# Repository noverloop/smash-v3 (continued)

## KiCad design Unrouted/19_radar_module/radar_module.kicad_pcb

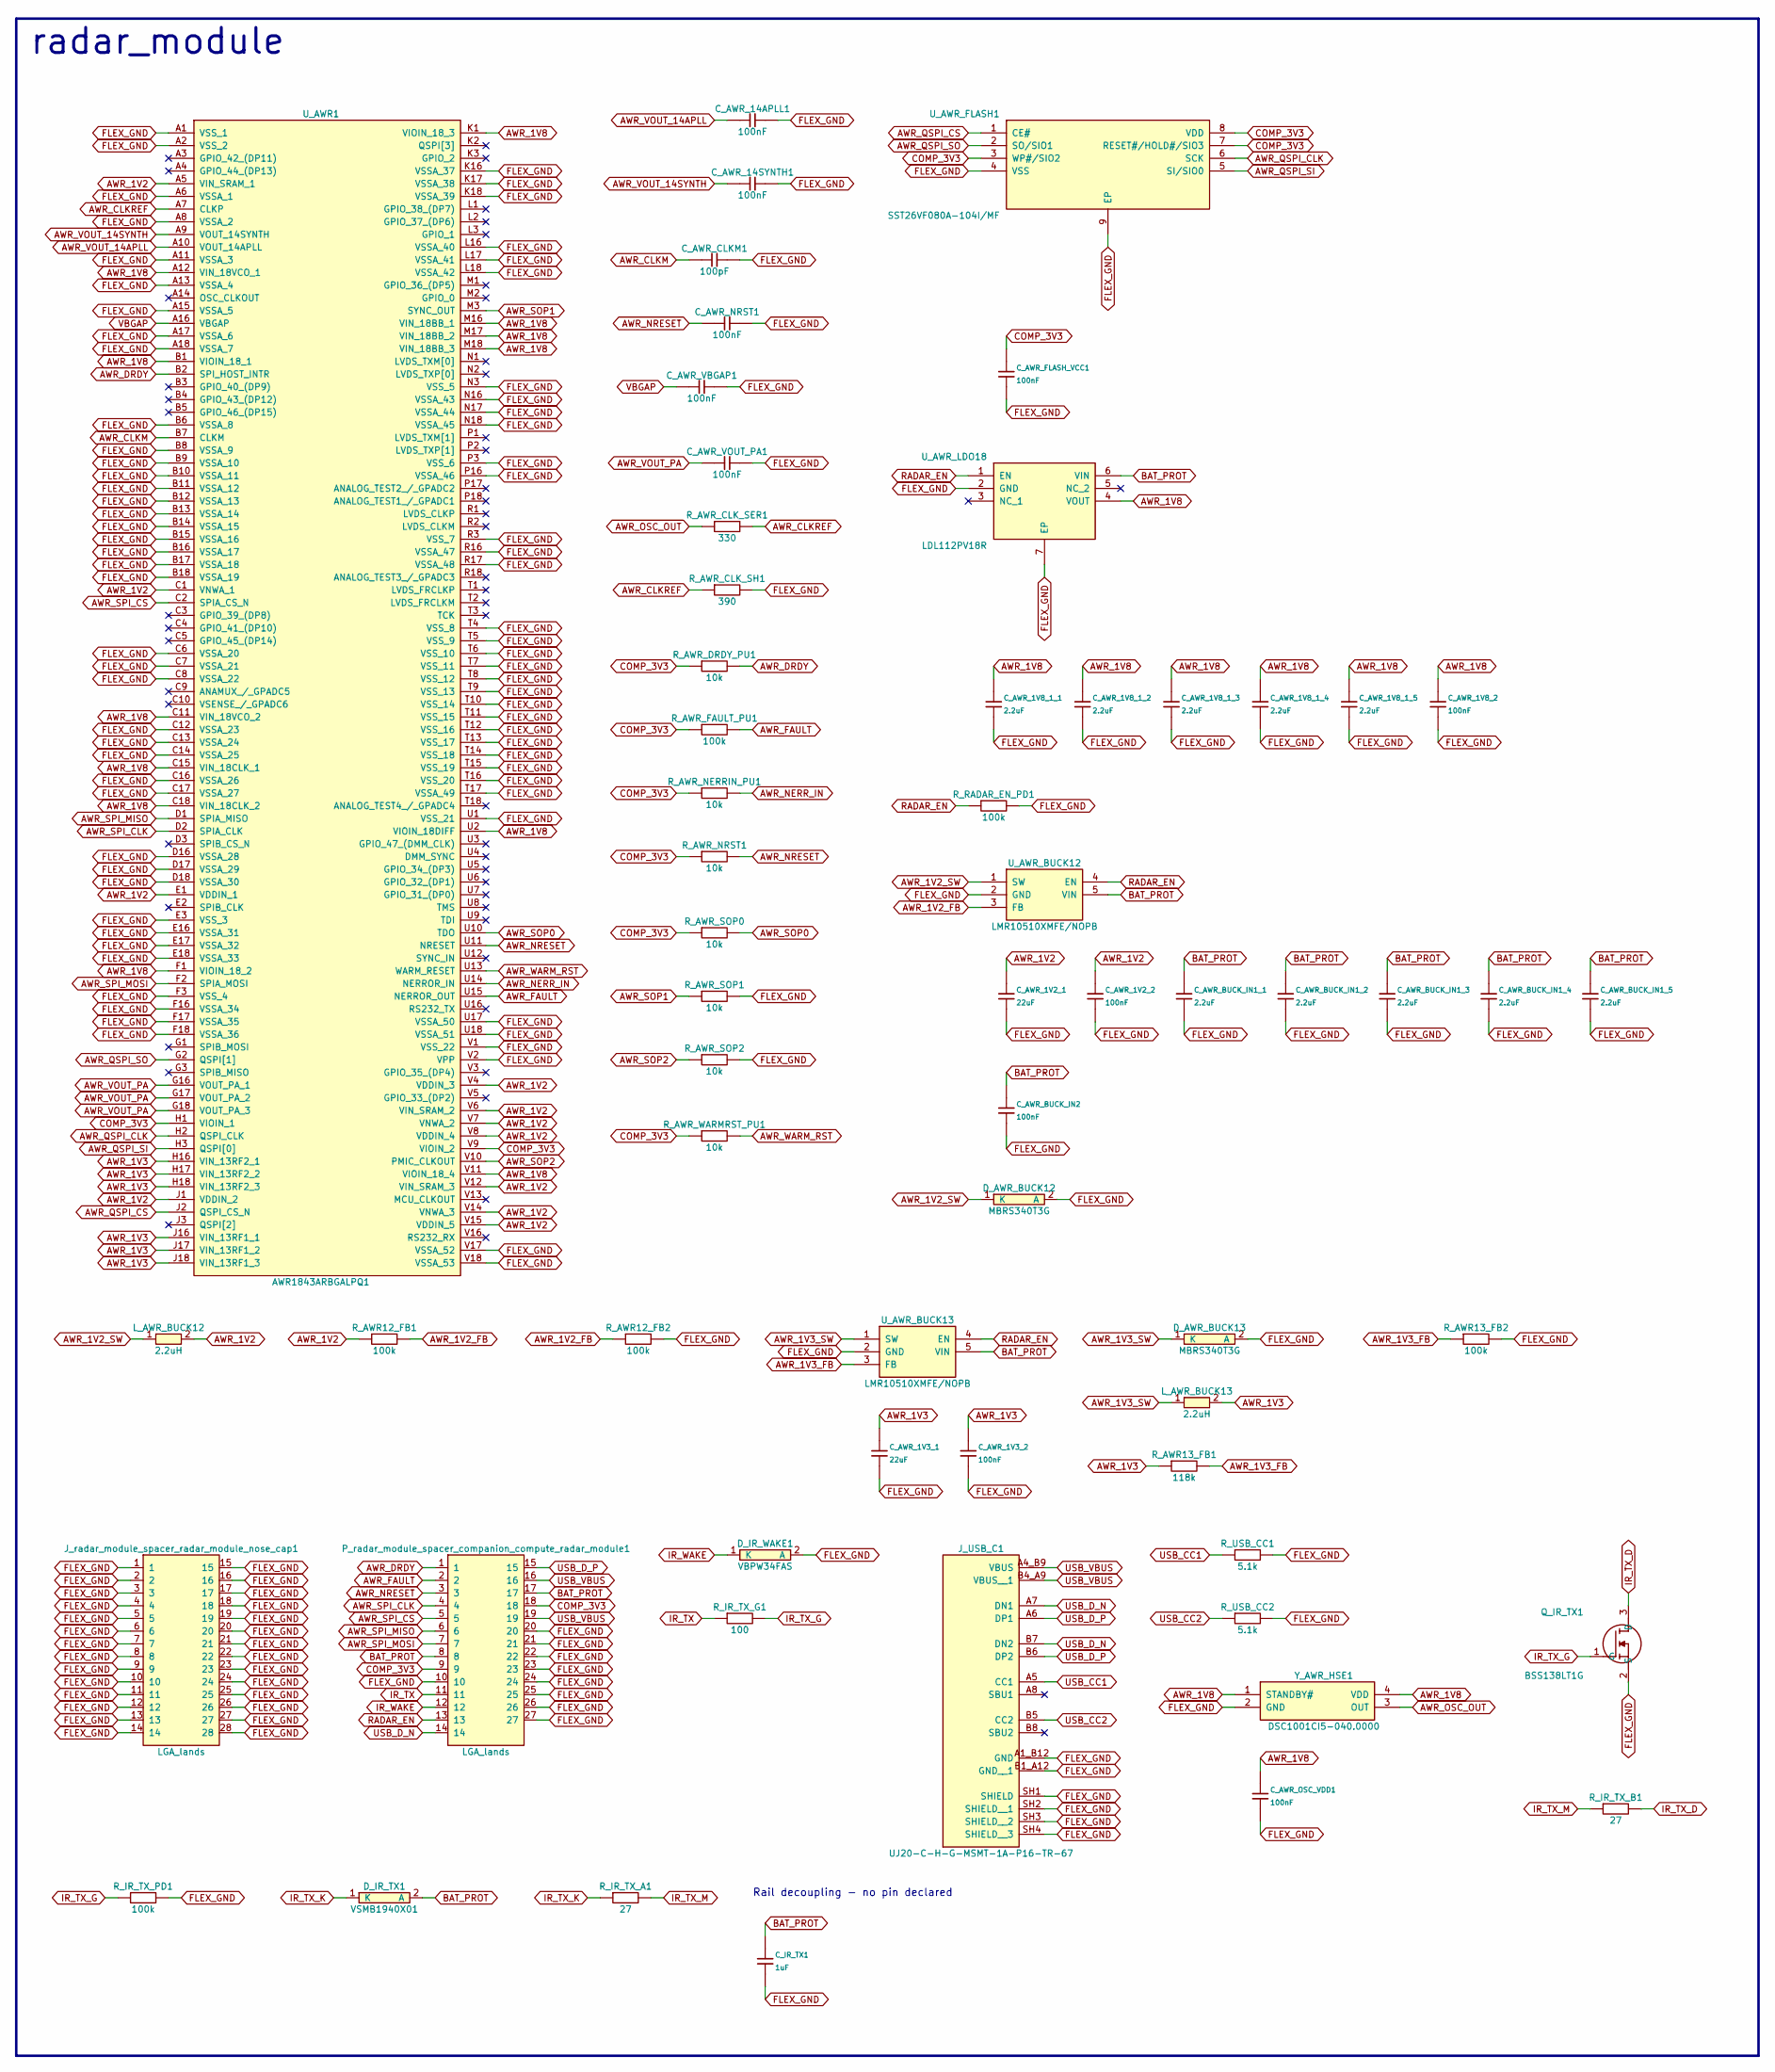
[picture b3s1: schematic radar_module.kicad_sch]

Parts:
C_AWR_1V2_1, C_AWR_1V3_1: 22uF; Capacitor_Tantalum_SMD_CP_EIA-3528-12_Kemet-T; MPN T491T 22uF (3528-12 thinnest variant)
C_AWR_1V2_2, C_AWR_1V3_2, C_AWR_1V8_2, C_AWR_14APLL1, C_AWR_14SYNTH1: 100nF; Capacitor_SMD_C_0402_1005Metric; MPN C0402 X7R 100nF
C_AWR_1V8_1_1, C_AWR_1V8_1_2, C_AWR_1V8_1_3, C_AWR_1V8_1_4, C_AWR_1V8_1_5: 2.2uF; Capacitor_SMD_C_0603_1608Metric; MPN C-Series MIL-PRF-32535 X7R 0603 2.2uF
C_AWR_BUCK_IN1_1, C_AWR_BUCK_IN1_2, C_AWR_BUCK_IN1_3, C_AWR_BUCK_IN1_4, C_AWR_BUCK_IN1_5: 2.2uF; Capacitor_SMD_C_0603_1608Metric; MPN C-Series MIL-PRF-32535 X7R 0603 2.2uF
C_AWR_BUCK_IN2: 100nF; Capacitor_SMD_C_0402_1005Metric; MPN C0402 X7R 100nF
C_AWR_CLKM1: 100pF; Capacitor_SMD_C_0603_1608Metric; MPN SQCSVA 100pF
C_AWR_FLASH_VCC1: 100nF; Capacitor_SMD_C_0402_1005Metric; MPN C0402 X7R 100nF
C_AWR_NRST1: 100nF; Capacitor_SMD_C_0402_1005Metric; MPN C0402 X7R 100nF
C_AWR_OSC_VDD1: 100nF; Capacitor_SMD_C_0402_1005Metric; MPN C0402 X7R 100nF
C_AWR_VBGAP1: 100nF; Capacitor_SMD_C_0402_1005Metric; MPN C0402 X7R 100nF
C_AWR_VOUT_PA1: 100nF; Capacitor_SMD_C_0402_1005Metric; MPN C0402 X7R 100nF
C_IR_TX1: 1uF; Capacitor_SMD_C_0805_2012Metric; MPN C-Series MIL-PRF-32535 X7R 0805 1uF
D_AWR_BUCK12, D_AWR_BUCK13: MBRS340T3G; DIOM8059X261N; MPN MBRS340T3G
D_IR_TX1: VSMB1940X01; MPN VSMB1940X01
D_IR_WAKE1: VBPW34FAS; MPN VBPW34FAS
J_USB_C1: UJ20-C-H-G-MSMT-1A-P16-TR-67; SAMESKY_UJ20-C-H-G-MSMT-1A-P16-TR-67; MPN UJ20-C-H-G-MSMT-1A-P16-TR-67
J_radar_module_spacer_radar_module_nose_cap1: LGA_lands; J_radar_module_spacer_radar_module_nose_cap; MPN LGA_lands
L_AWR_BUCK12, L_AWR_BUCK13: 2.2uH; Inductor_SMD_L_2012_2.0x1.25mm; MPN TMS201210ALM-2R2MTAA
P_radar_module_spacer_companion_compute_radar_module1: LGA_lands; P_radar_module_spacer_companion_compute_radar_module; MPN LGA_lands
Q_IR_TX1: BSS138LT1G; SOT96P237X111-3N; MPN BSS138LT1G
R_AWR12_FB1, R_AWR12_FB2, R_AWR13_FB2: 100k; Resistor_SMD_R_0402_1005Metric; MPN CRCW0402 100k 1% e3
R_AWR13_FB1: 118k; Resistor_SMD_R_0402_1005Metric; MPN CRCW0402 118k 1% e3
R_AWR_CLK_SER1: 330; Resistor_SMD_R_0402_1005Metric; MPN CRCW0402 330 1% e3
R_AWR_CLK_SH1: 390; Resistor_SMD_R_0402_1005Metric; MPN CRCW0402 390 1% e3
R_AWR_DRDY_PU1: 10k; Resistor_SMD_R_0402_1005Metric; MPN CRCW0402 10k 1% e3
R_AWR_FAULT_PU1: 100k; Resistor_SMD_R_0402_1005Metric; MPN CRCW0402 100k 1% e3
R_AWR_NERRIN_PU1: 10k; Resistor_SMD_R_0402_1005Metric; MPN CRCW0402 10k 1% e3
R_AWR_NRST1: 10k; Resistor_SMD_R_0402_1005Metric; MPN CRCW0402 10k 1% e3
R_AWR_SOP0, R_AWR_SOP1, R_AWR_SOP2: 10k; Resistor_SMD_R_0402_1005Metric; MPN CRCW0402 10k 1% e3
R_AWR_WARMRST_PU1: 10k; Resistor_SMD_R_0402_1005Metric; MPN CRCW0402 10k 1% e3
R_IR_TX_A1: 27; Resistor_SMD_R_0402_1005Metric; MPN CRCW0402 27 1% e3
R_IR_TX_B1: 27; Resistor_SMD_R_0402_1005Metric; MPN CRCW0402 27 1% e3
R_IR_TX_G1: 100; Resistor_SMD_R_0402_1005Metric; MPN CRCW0402 100 1% e3
R_IR_TX_PD1: 100k; Resistor_SMD_R_0402_1005Metric; MPN CRCW0402 100k 1% e3
R_RADAR_EN_PD1: 100k; Resistor_SMD_R_0402_1005Metric; MPN CRCW0402 100k 1% e3
R_USB_CC1, R_USB_CC2: 5.1k; Resistor_SMD_R_0402_1005Metric; MPN CRCW0402 5.1k 1% e3
U_AWR1: AWR1843ARBGALPQ1; BGA180C80P18X18_1500X1500X96; MPN AWR1843ARBGALPQ1
U_AWR_BUCK12, U_AWR_BUCK13: LMR10510XMFE/NOPB; SOT95P280X145-5N; MPN LMR10510XMFE/NOPB
U_AWR_FLASH1: SST26VF080A-104I/MF; SON127P600X500X80-9N-D; MPN SST26VF080A-104I/MF
U_AWR_LDO18: LDL112PV18R; SON95P300X300X100-7N-D; MPN LDL112PV18R
Y_AWR_HSE1: DSC1001CI5-040.0000; DSC1001CI50080000; MPN DSC1001CI5-040.0000

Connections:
AWR_1V2: C_AWR_1V2_1.1, C_AWR_1V2_2.1, L_AWR_BUCK12.2, R_AWR12_FB1.1, U_AWR1.A5 (VIN_SRAM_1), U_AWR1.C1 (VNWA_1), U_AWR1.E1 (VDDIN_1), U_AWR1.J1 (VDDIN_2), U_AWR1.V4 (VDDIN_3), U_AWR1.V6 (VIN_SRAM_2), U_AWR1.V7 (VNWA_2), U_AWR1.V8 (VDDIN_4), U_AWR1.V12 (VIN_SRAM_3), U_AWR1.V14 (VNWA_3), U_AWR1.V15 (VDDIN_5)
AWR_1V2_FB: R_AWR12_FB1.2, R_AWR12_FB2.1, U_AWR_BUCK12.3 (FB)
AWR_1V2_SW: D_AWR_BUCK12.1 (K), L_AWR_BUCK12.1, U_AWR_BUCK12.1 (SW)
AWR_1V3: C_AWR_1V3_1.1, C_AWR_1V3_2.1, L_AWR_BUCK13.2, R_AWR13_FB1.1, U_AWR1.H16 (VIN_13RF2_1), U_AWR1.H17 (VIN_13RF2_2), U_AWR1.H18 (VIN_13RF2_3), U_AWR1.J16 (VIN_13RF1_1), U_AWR1.J17 (VIN_13RF1_2), U_AWR1.J18 (VIN_13RF1_3)
AWR_1V3_FB: R_AWR13_FB1.2, R_AWR13_FB2.1, U_AWR_BUCK13.3 (FB)
AWR_1V3_SW: D_AWR_BUCK13.1 (K), L_AWR_BUCK13.1, U_AWR_BUCK13.1 (SW)
AWR_1V8: C_AWR_1V8_1_1.1, C_AWR_1V8_1_2.1, C_AWR_1V8_1_3.1, C_AWR_1V8_1_4.1, C_AWR_1V8_1_5.1, C_AWR_1V8_2.1, C_AWR_OSC_VDD1.1, U_AWR1.A12 (VIN_18VCO_1), U_AWR1.B1 (VIOIN_18_1), U_AWR1.C11 (VIN_18VCO_2), U_AWR1.C15 (VIN_18CLK_1), U_AWR1.C18 (VIN_18CLK_2), U_AWR1.F1 (VIOIN_18_2), U_AWR1.K1 (VIOIN_18_3), U_AWR1.M16 (VIN_18BB_1), U_AWR1.M17 (VIN_18BB_2), U_AWR1.M18 (VIN_18BB_3), U_AWR1.U2 (VIOIN_18DIFF), U_AWR1.V11 (VIOIN_18_4), U_AWR_LDO18.4 (VOUT), Y_AWR_HSE1.1 (STANDBY#), Y_AWR_HSE1.4 (VDD)
AWR_CLKM: C_AWR_CLKM1.1, U_AWR1.B7 (CLKM)
AWR_CLKREF: R_AWR_CLK_SER1.2, R_AWR_CLK_SH1.1, U_AWR1.A7 (CLKP)
AWR_DRDY: P_radar_module_spacer_companion_compute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.1, R_AWR_DRDY_PU1.2, U_AWR1.B2 (SPI_HOST_INTR)
AWR_FAULT: P_radar_module_spacer_companion_compute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.2, R_AWR_FAULT_PU1.2, U_AWR1.U15 (NERROR_OUT)
AWR_NERR_IN: R_AWR_NERRIN_PU1.2, U_AWR1.U14 (NERROR_IN)
AWR_NRESET: C_AWR_NRST1.1, P_radar_module_spacer_companion_compute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.3, R_AWR_NRST1.2, U_AWR1.U11 (NRESET)
AWR_OSC_OUT: R_AWR_CLK_SER1.1, Y_AWR_HSE1.3 (OUT)
AWR_QSPI_CLK: U_AWR1.H2 (QSPI_CLK), U_AWR_FLASH1.6 (SCK)
AWR_QSPI_CS: U_AWR1.J2 (QSPI_CS_N), U_AWR_FLASH1.1 (CE#)
AWR_QSPI_SI: U_AWR1.H3 (QSPI[0]), U_AWR_FLASH1.5 (SI/SIO0)
AWR_QSPI_SO: U_AWR1.G2 (QSPI[1]), U_AWR_FLASH1.2 (SO/SIO1)
AWR_SOP0: R_AWR_SOP0.2, U_AWR1.U10 (TDO)
AWR_SOP1: R_AWR_SOP1.1, U_AWR1.M3 (SYNC_OUT)
AWR_SOP2: R_AWR_SOP2.1, U_AWR1.V10 (PMIC_CLKOUT)
AWR_SPI_CLK: P_radar_module_spacer_companion_compute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.4, U_AWR1.D2 (SPIA_CLK)
AWR_SPI_CS: P_radar_module_spacer_companion_compute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.5, U_AWR1.C2 (SPIA_CS_N)
AWR_SPI_MISO: P_radar_module_spacer_companion_compute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.6, U_AWR1.D1 (SPIA_MISO)
AWR_SPI_MOSI: P_radar_module_spacer_companion_compute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.7, U_AWR1.F2 (SPIA_MOSI)
AWR_VOUT_14APLL: C_AWR_14APLL1.1, U_AWR1.A10 (VOUT_14APLL)
AWR_VOUT_14SYNTH: C_AWR_14SYNTH1.1, U_AWR1.A9 (VOUT_14SYNTH)
AWR_VOUT_PA: C_AWR_VOUT_PA1.1, U_AWR1.G16 (VOUT_PA_1), U_AWR1.G17 (VOUT_PA_2), U_AWR1.G18 (VOUT_PA_3)
AWR_WARM_RST: R_AWR_WARMRST_PU1.2, U_AWR1.U13 (WARM_RESET)
BAT_PROT: C_AWR_BUCK_IN1_1.1, C_AWR_BUCK_IN1_2.1, C_AWR_BUCK_IN1_3.1, C_AWR_BUCK_IN1_4.1, C_AWR_BUCK_IN1_5.1, C_AWR_BUCK_IN2.1, C_IR_TX1.1, D_IR_TX1.2 (A), P_radar_module_spacer_companion_compute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.8, P_radar_module_spacer_companion_compute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.17, U_AWR_BUCK12.5 (VIN), U_AWR_BUCK13.5 (VIN), U_AWR_LDO18.6 (VIN)
COMP_3V3: C_AWR_FLASH_VCC1.1, P_radar_module_spacer_companion_compute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.9, P_radar_module_spacer_companion_compute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.18, R_AWR_DRDY_PU1.1, R_AWR_FAULT_PU1.1, R_AWR_NERRIN_PU1.1, R_AWR_NRST1.1, R_AWR_SOP0.1, R_AWR_WARMRST_PU1.1, U_AWR1.H1 (VIOIN_1), U_AWR1.V9 (VIOIN_2), U_AWR_FLASH1.3 (WP#/SIO2), U_AWR_FLASH1.7 (RESET#/HOLD#/SIO3), U_AWR_FLASH1.8 (VDD)
FLEX_GND: C_AWR_1V2_1.2, C_AWR_1V2_2.2, C_AWR_1V3_1.2, C_AWR_1V3_2.2, C_AWR_1V8_1_1.2, C_AWR_1V8_1_2.2, C_AWR_1V8_1_3.2, C_AWR_1V8_1_4.2, C_AWR_1V8_1_5.2, C_AWR_1V8_2.2, C_AWR_14APLL1.2, C_AWR_14SYNTH1.2, C_AWR_BUCK_IN1_1.2, C_AWR_BUCK_IN1_2.2, C_AWR_BUCK_IN1_3.2, C_AWR_BUCK_IN1_4.2, C_AWR_BUCK_IN1_5.2, C_AWR_BUCK_IN2.2, C_AWR_CLKM1.2, C_AWR_FLASH_VCC1.2, C_AWR_NRST1.2, C_AWR_OSC_VDD1.2, C_AWR_VBGAP1.2, C_AWR_VOUT_PA1.2, C_IR_TX1.2, D_AWR_BUCK12.2 (A), D_AWR_BUCK13.2 (A), D_IR_WAKE1.2 (A), J_USB_C1.A1_B12 (GND), J_USB_C1.B1_A12 (GND__1), J_USB_C1.SH1 (SHIELD), J_USB_C1.SH2 (SHIELD__1), J_USB_C1.SH3 (SHIELD__2), J_USB_C1.SH4 (SHIELD__3), J_radar_module_spacer_radar_module_nose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.1, J_radar_module_spacer_radar_module_nose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.2, J_radar_module_spacer_radar_module_nose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.3, J_radar_module_spacer_radar_module_nose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.4, J_radar_module_spacer_radar_module_nose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.5, J_radar_module_spacer_radar_module_nose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.6, J_radar_module_spacer_radar_module_nose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.7, J_radar_module_spacer_radar_module_nose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.8, J_radar_module_spacer_radar_module_nose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.9, J_radar_module_spacer_radar_module_nose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.10, J_radar_module_spacer_radar_module_nose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.11, J_radar_module_spacer_radar_module_nose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.12, J_radar_module_spacer_radar_module_nose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.13, J_radar_module_spacer_radar_module_nose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.14, J_radar_module_spacer_radar_module_nose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.15, J_radar_module_spacer_radar_module_nose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.16, J_radar_module_spacer_radar_module_nose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.17, J_radar_module_spacer_radar_module_nose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.18, J_radar_module_spacer_radar_module_nose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.19, J_radar_module_spacer_radar_module_nose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.20, J_radar_module_spacer_radar_module_nose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.21, J_radar_module_spacer_radar_module_nose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.22, J_radar_module_spacer_radar_module_nose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.23, J_radar_module_spacer_radar_module_nose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.24, J_radar_module_spacer_radar_module_nose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.25, J_radar_module_spacer_radar_module_nose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.26, J_radar_module_spacer_radar_module_nose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.27, J_radar_module_spacer_radar_module_nose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.28, P_radar_module_spacer_companion_compute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.10, P_radar_module_spacer_companion_compute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.20, P_radar_module_spacer_companion_compute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.21, P_radar_module_spacer_companion_compute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.22, P_radar_module_spacer_companion_compute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.23, P_radar_module_spacer_companion_compute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.24, P_radar_module_spacer_companion_compute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.25, P_radar_module_spacer_companion_compute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.26, P_radar_module_spacer_companion_compute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.27, Q_IR_TX1.2 (S), R_AWR12_FB2.2, R_AWR13_FB2.2, R_AWR_CLK_SH1.2, R_AWR_SOP1.2, R_AWR_SOP2.2, R_IR_TX_PD1.2, R_RADAR_EN_PD1.2, R_USB_CC1.2, R_USB_CC2.2, U_AWR1.A1 (VSS_1), U_AWR1.A2 (VSS_2), U_AWR1.A6 (VSSA_1), U_AWR1.A8 (VSSA_2), U_AWR1.A11 (VSSA_3), U_AWR1.A13 (VSSA_4), U_AWR1.A15 (VSSA_5), U_AWR1.A17 (VSSA_6), U_AWR1.A18 (VSSA_7), U_AWR1.B6 (VSSA_8), U_AWR1.B8 (VSSA_9), U_AWR1.B9 (VSSA_10), U_AWR1.B10 (VSSA_11), U_AWR1.B11 (VSSA_12), U_AWR1.B12 (VSSA_13), U_AWR1.B13 (VSSA_14), U_AWR1.B14 (VSSA_15), U_AWR1.B15 (VSSA_16), U_AWR1.B16 (VSSA_17), U_AWR1.B17 (VSSA_18), U_AWR1.B18 (VSSA_19), U_AWR1.C6 (VSSA_20), U_AWR1.C7 (VSSA_21), U_AWR1.C8 (VSSA_22), U_AWR1.C12 (VSSA_23), U_AWR1.C13 (VSSA_24), U_AWR1.C14 (VSSA_25), U_AWR1.C16 (VSSA_26), U_AWR1.C17 (VSSA_27), U_AWR1.D16 (VSSA_28), U_AWR1.D17 (VSSA_29), U_AWR1.D18 (VSSA_30), U_AWR1.E3 (VSS_3), U_AWR1.E16 (VSSA_31), U_AWR1.E17 (VSSA_32), U_AWR1.E18 (VSSA_33), U_AWR1.F3 (VSS_4), U_AWR1.F16 (VSSA_34), U_AWR1.F17 (VSSA_35), U_AWR1.F18 (VSSA_36), U_AWR1.K16 (VSSA_37), U_AWR1.K17 (VSSA_38), U_AWR1.K18 (VSSA_39), U_AWR1.L16 (VSSA_40), U_AWR1.L17 (VSSA_41), U_AWR1.L18 (VSSA_42), U_AWR1.N3 (VSS_5), U_AWR1.N16 (VSSA_43), U_AWR1.N17 (VSSA_44), U_AWR1.N18 (VSSA_45), U_AWR1.P3 (VSS_6), U_AWR1.P16 (VSSA_46), U_AWR1.R3 (VSS_7), U_AWR1.R16 (VSSA_47), U_AWR1.R17 (VSSA_48), U_AWR1.T4 (VSS_8), U_AWR1.T5 (VSS_9), U_AWR1.T6 (VSS_10), U_AWR1.T7 (VSS_11), U_AWR1.T8 (VSS_12), U_AWR1.T9 (VSS_13), U_AWR1.T10 (VSS_14), U_AWR1.T11 (VSS_15), U_AWR1.T12 (VSS_16), U_AWR1.T13 (VSS_17), U_AWR1.T14 (VSS_18), U_AWR1.T15 (VSS_19), U_AWR1.T16 (VSS_20), U_AWR1.T17 (VSSA_49), U_AWR1.U1 (VSS_21), U_AWR1.U17 (VSSA_50), U_AWR1.U18 (VSSA_51), U_AWR1.V1 (VSS_22), U_AWR1.V2 (VPP), U_AWR1.V17 (VSSA_52), U_AWR1.V18 (VSSA_53), U_AWR_BUCK12.2 (GND), U_AWR_BUCK13.2 (GND), U_AWR_FLASH1.4 (VSS), U_AWR_FLASH1.9 (EP), U_AWR_LDO18.2 (GND), U_AWR_LDO18.7 (EP), Y_AWR_HSE1.2 (GND)
IR_TX: P_radar_module_spacer_companion_compute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.11, R_IR_TX_G1.1
IR_TX_D: Q_IR_TX1.3 (D), R_IR_TX_B1.2
IR_TX_G: Q_IR_TX1.1 (G), R_IR_TX_G1.2, R_IR_TX_PD1.1
IR_TX_K: D_IR_TX1.1 (K), R_IR_TX_A1.1
IR_TX_M: R_IR_TX_A1.2, R_IR_TX_B1.1
IR_WAKE: D_IR_WAKE1.1 (K), P_radar_module_spacer_companion_compute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.12
RADAR_EN: P_radar_module_spacer_companion_compute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.13, R_RADAR_EN_PD1.1, U_AWR_BUCK12.4 (EN), U_AWR_BUCK13.4 (EN), U_AWR_LDO18.1 (EN)
USB_CC1: J_USB_C1.A5 (CC1), R_USB_CC1.1
USB_CC2: J_USB_C1.B5 (CC2), R_USB_CC2.1
USB_D_N: J_USB_C1.A7 (DN1), J_USB_C1.B7 (DN2), P_radar_module_spacer_companion_compute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.14
USB_D_P: J_USB_C1.A6 (DP1), J_USB_C1.B6 (DP2), P_radar_module_spacer_companion_compute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.15
USB_VBUS: J_USB_C1.A4_B9 (VBUS), J_USB_C1.B4_A9 (VBUS__1), P_radar_module_spacer_companion_compute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.16, P_radar_module_spacer_companion_compute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.19
VBGAP: C_AWR_VBGAP1.1, U_AWR1.A16 (VBGAP)

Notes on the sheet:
radar_module
Rail decoupling - no pin declared

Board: 20 copper layers, 64 parts (54 on the bottom side), 45 nets, no tracks yet.

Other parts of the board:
MH1, MH2: smash_mech_potting

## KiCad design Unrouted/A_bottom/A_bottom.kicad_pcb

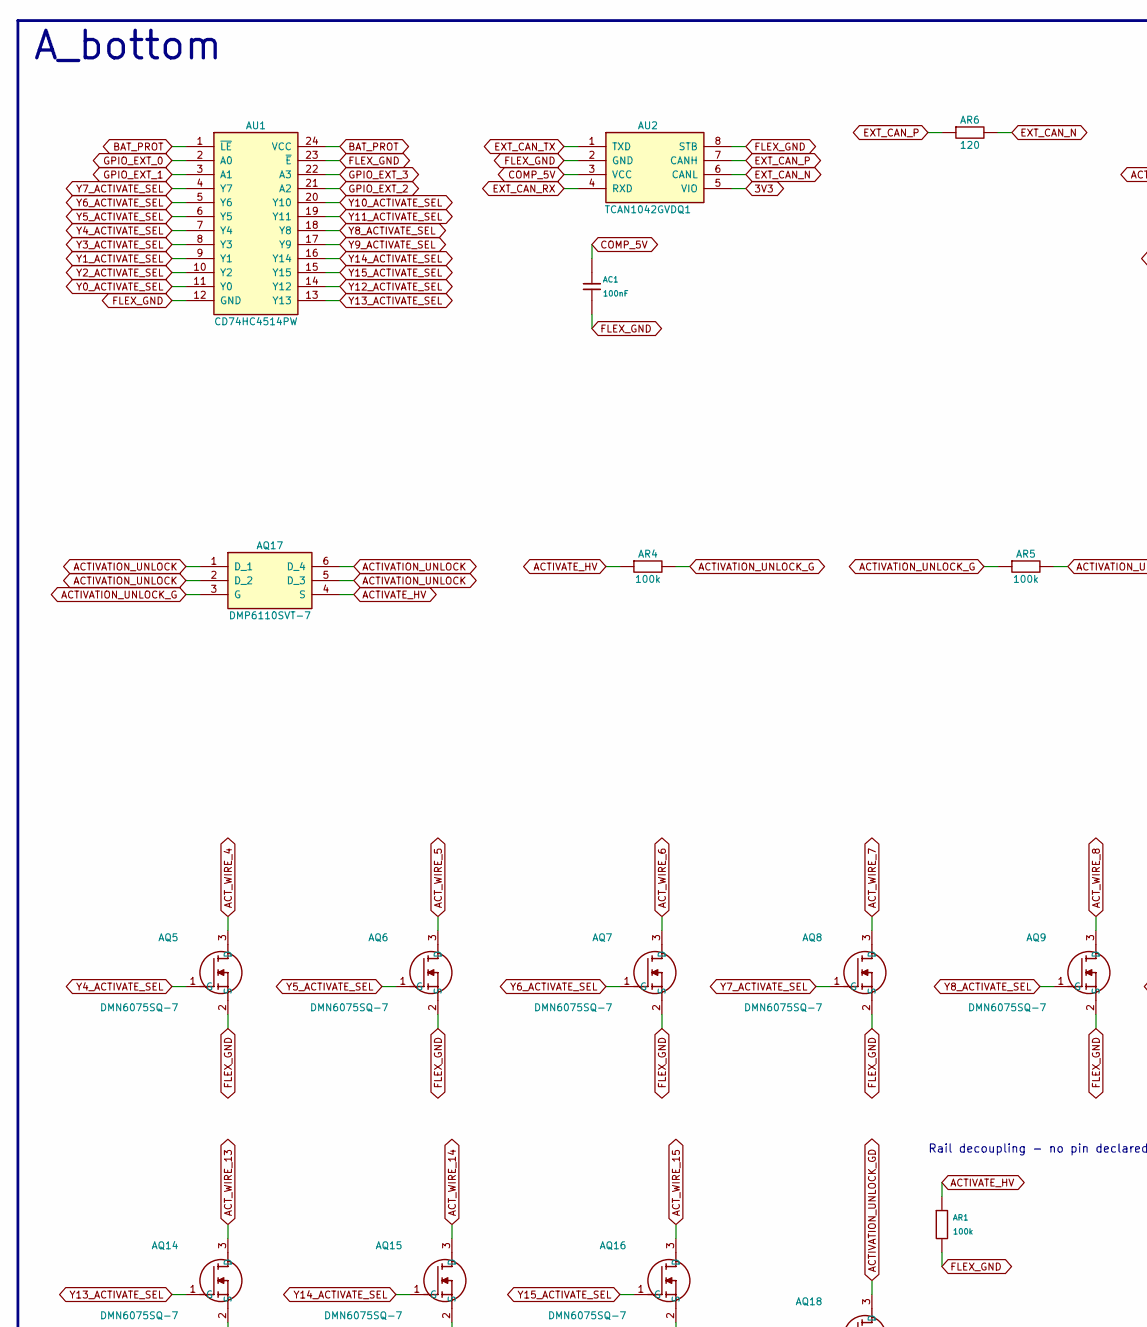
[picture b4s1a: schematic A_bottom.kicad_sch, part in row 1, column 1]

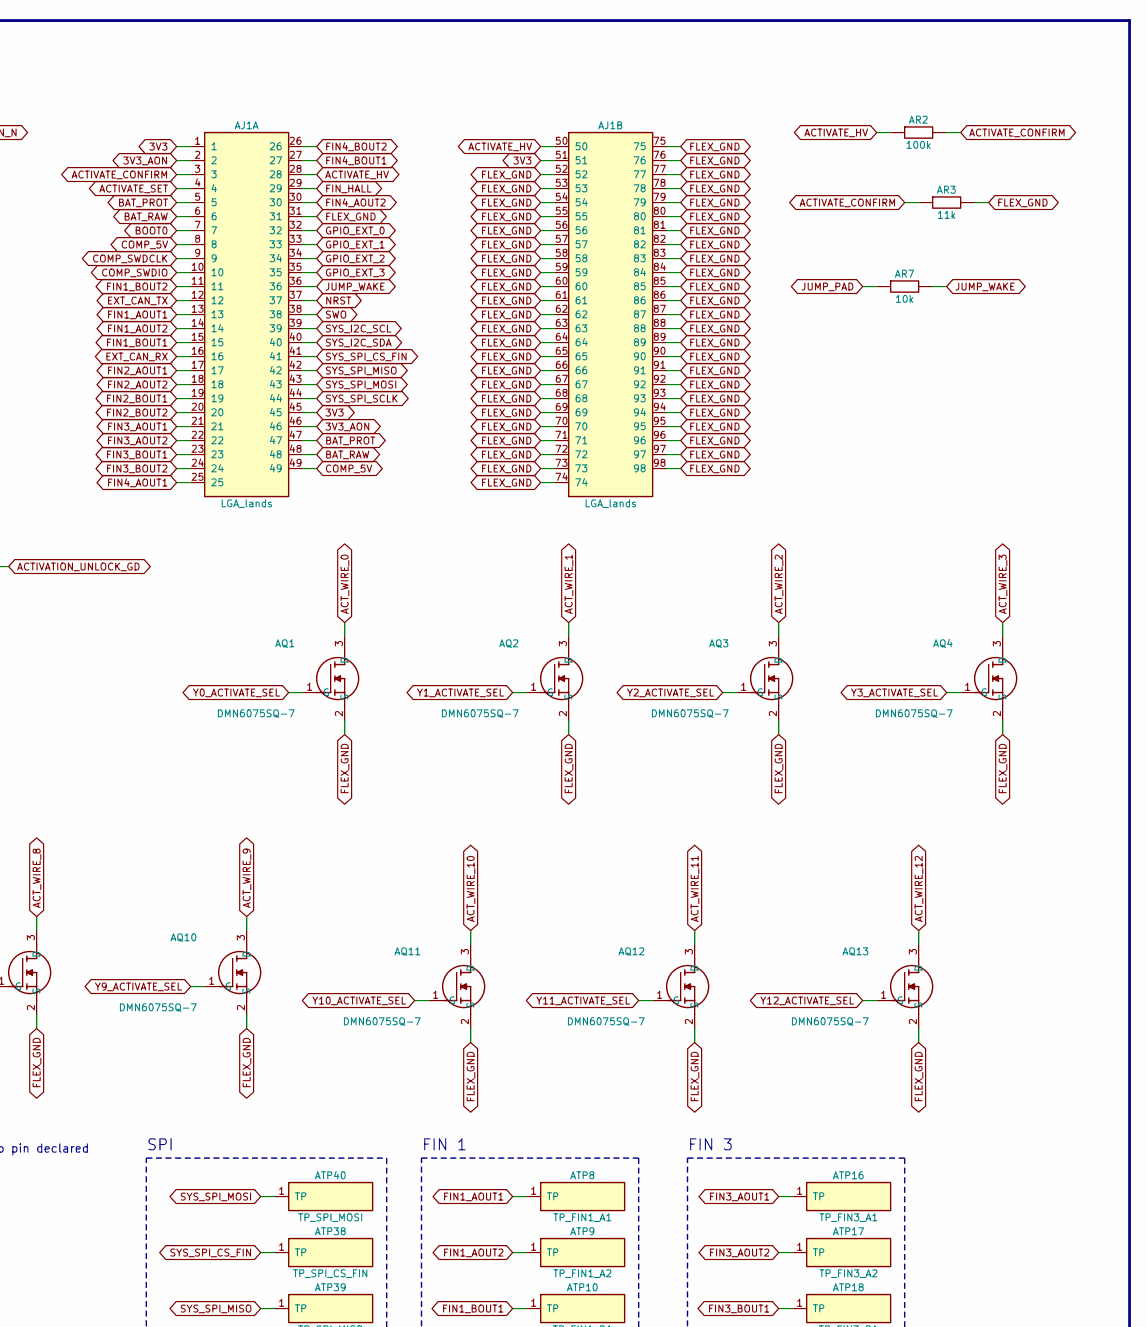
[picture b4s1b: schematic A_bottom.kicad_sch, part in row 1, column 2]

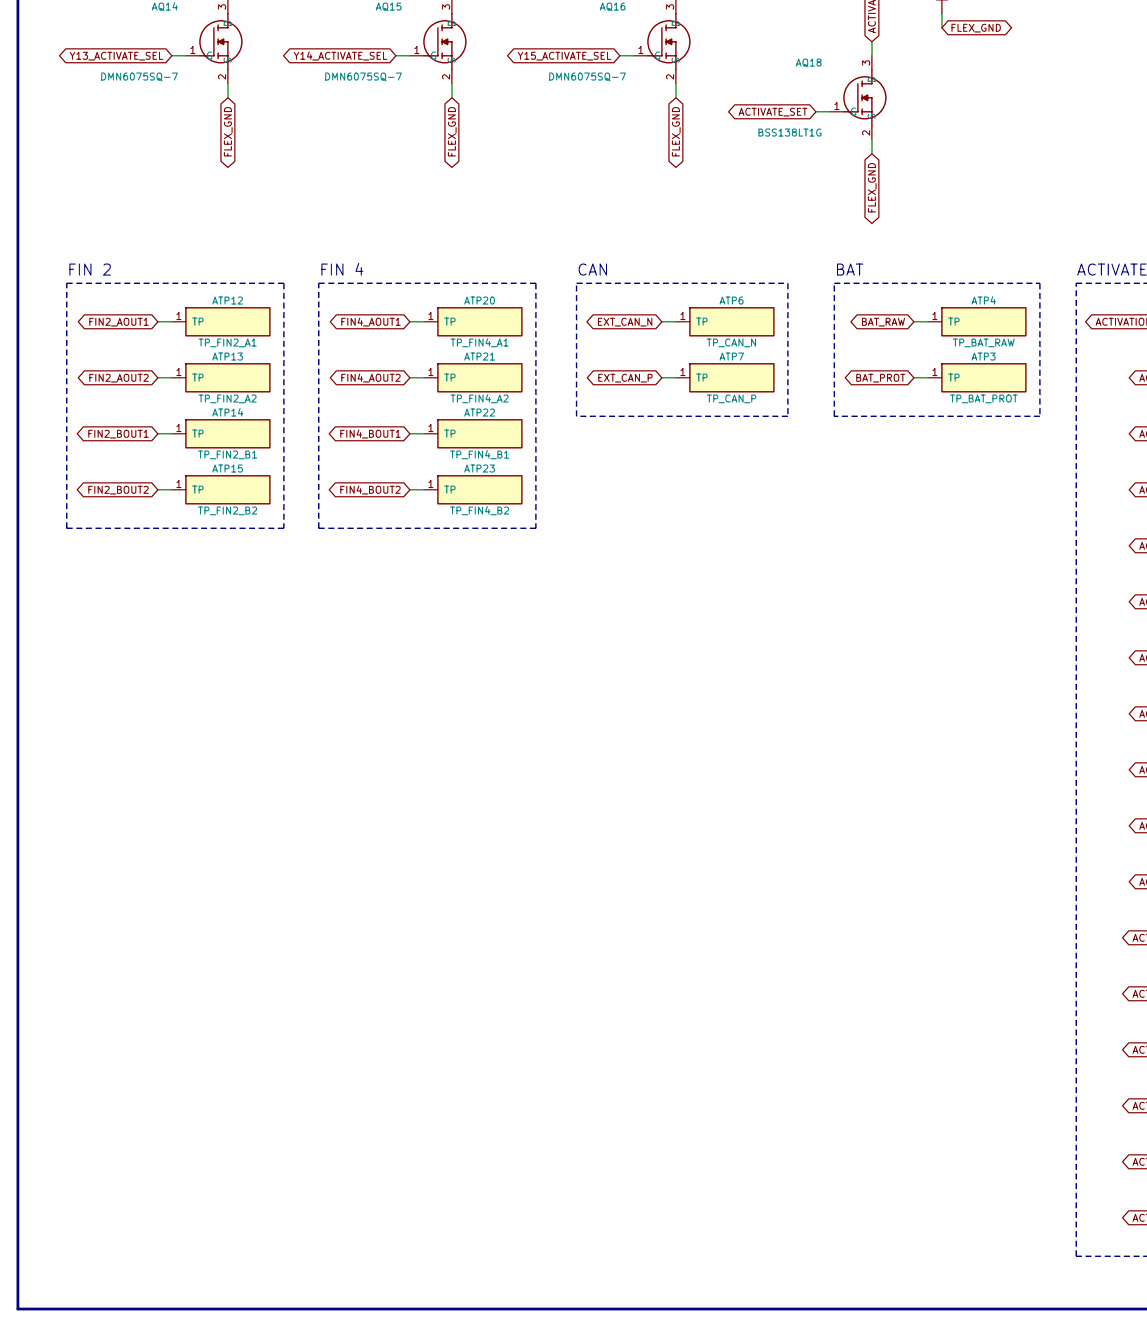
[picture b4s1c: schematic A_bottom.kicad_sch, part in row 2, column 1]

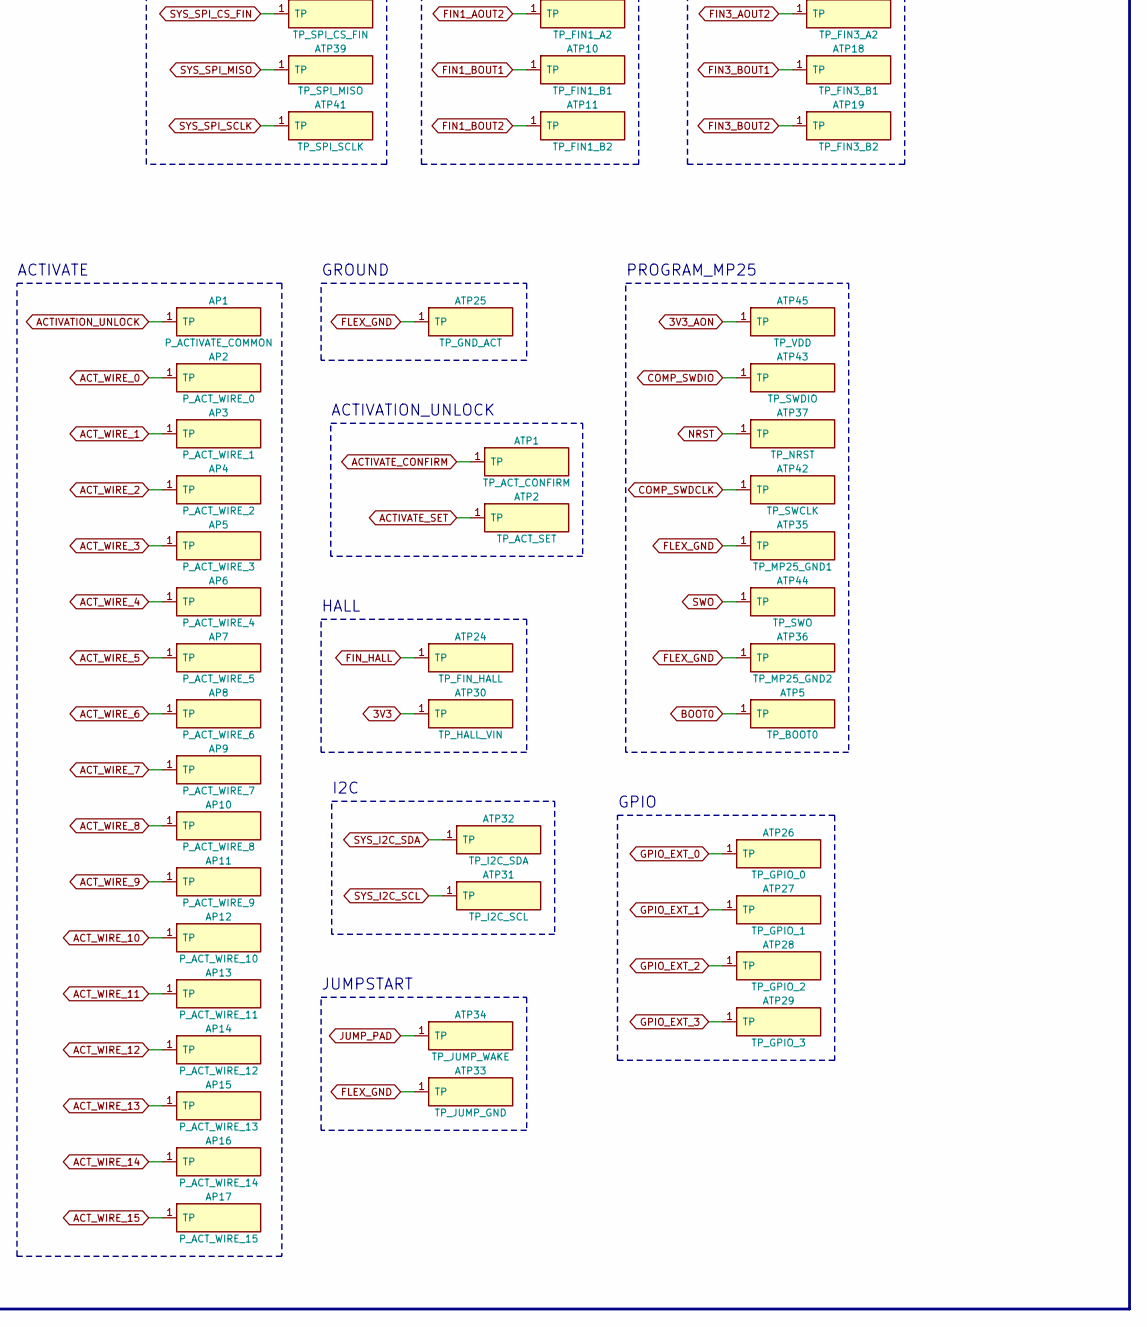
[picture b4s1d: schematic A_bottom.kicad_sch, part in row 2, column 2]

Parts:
AC1: 100nF; Capacitor_SMD_C_0402_1005Metric; MPN C0402 X7R 100nF
AJ1: LGA_lands; J_aft_end_board_spacer_aft_end_board_activation_interface; MPN LGA_lands
AP1: P_ACTIVATE_COMMON; Pogo_Pad_D2.0mm
AP2: P_ACT_WIRE_0; Pogo_Pad_S2.0mm
AP3: P_ACT_WIRE_1; Pogo_Pad_D2.0mm
AP4: P_ACT_WIRE_2; Pogo_Pad_D2.0mm
AP5: P_ACT_WIRE_3; Pogo_Pad_D2.0mm
AP6: P_ACT_WIRE_4; Pogo_Pad_D2.0mm
AP7: P_ACT_WIRE_5; Pogo_Pad_D2.0mm
AP8: P_ACT_WIRE_6; Pogo_Pad_D2.0mm
AP9: P_ACT_WIRE_7; Pogo_Pad_D2.0mm
AP10: P_ACT_WIRE_8; Pogo_Pad_D2.0mm
AP11: P_ACT_WIRE_9; Pogo_Pad_D2.0mm
AP12: P_ACT_WIRE_10; Pogo_Pad_D2.0mm
AP13: P_ACT_WIRE_11; Pogo_Pad_D2.0mm
AP14: P_ACT_WIRE_12; Pogo_Pad_D2.0mm
AP15: P_ACT_WIRE_13; Pogo_Pad_D2.0mm
AP16: P_ACT_WIRE_14; Pogo_Pad_D2.0mm
AP17: P_ACT_WIRE_15; Pogo_Pad_D2.0mm
AQ1, AQ2, AQ3, AQ4, AQ5, AQ6, AQ7, AQ8, AQ9, AQ10, AQ11, AQ12, AQ13, AQ14, AQ15, AQ16: DMN6075SQ-7; SOT96P240X110-3N; MPN DMN6075SQ-7
AQ17: DMP6110SVT-7; SOT95P280X100-6N; MPN DMP6110SVT-7
AQ18: BSS138LT1G; SOT96P237X111-3N; MPN BSS138LT1G
AR1, AR2, AR4, AR5: 100k; Resistor_SMD_R_0402_1005Metric; MPN CRCW0402 100k 1% e3
AR3: 11k; Resistor_SMD_R_0402_1005Metric; MPN CRCW0402 11k 1% e3
AR6: 120; Resistor_SMD_R_0402_1005Metric; MPN CRCW0402 120 1% e3
AR7: 10k; Resistor_SMD_R_0402_1005Metric; MPN CRCW0402 10k 1% e3
ATP1: TP_ACT_CONFIRM; Pogo_Pad_S2.0mm
ATP2: TP_ACT_SET; Pogo_Pad_D2.0mm
ATP3: TP_BAT_PROT; Pogo_Pad_D2.0mm
ATP4: TP_BAT_RAW; Pogo_Pad_S2.0mm
ATP5: TP_BOOT0; Pogo_Pad_D2.0mm
ATP6: TP_CAN_N; Pogo_Pad_S2.0mm
ATP7: TP_CAN_P; Pogo_Pad_D2.0mm
ATP8: TP_FIN1_A1; Pogo_Pad_S2.0mm
ATP9: TP_FIN1_A2; Pogo_Pad_D2.0mm
ATP10: TP_FIN1_B1; Pogo_Pad_D2.0mm
ATP11: TP_FIN1_B2; Pogo_Pad_D2.0mm
ATP12: TP_FIN2_A1; Pogo_Pad_S2.0mm
ATP13: TP_FIN2_A2; Pogo_Pad_D2.0mm
ATP14: TP_FIN2_B1; Pogo_Pad_D2.0mm
ATP15: TP_FIN2_B2; Pogo_Pad_D2.0mm
ATP16: TP_FIN3_A1; Pogo_Pad_S2.0mm
ATP17: TP_FIN3_A2; Pogo_Pad_D2.0mm
ATP18: TP_FIN3_B1; Pogo_Pad_D2.0mm
ATP19: TP_FIN3_B2; Pogo_Pad_D2.0mm
ATP20: TP_FIN4_A1; Pogo_Pad_S2.0mm
ATP21: TP_FIN4_A2; Pogo_Pad_D2.0mm
ATP22: TP_FIN4_B1; Pogo_Pad_D2.0mm
ATP23: TP_FIN4_B2; Pogo_Pad_D2.0mm
ATP24: TP_FIN_HALL; Pogo_Pad_S2.0mm
ATP25: TP_GND_ACT; Pogo_Pad_D2.0mm
ATP26: TP_GPIO_0; Pogo_Pad_S2.0mm
ATP27: TP_GPIO_1; Pogo_Pad_D2.0mm
ATP28: TP_GPIO_2; Pogo_Pad_D2.0mm
ATP29: TP_GPIO_3; Pogo_Pad_D2.0mm
ATP30: TP_HALL_VIN; Pogo_Pad_D2.0mm
ATP31: TP_I2C_SCL; Pogo_Pad_D2.0mm
ATP32: TP_I2C_SDA; Pogo_Pad_S2.0mm
ATP33: TP_JUMP_GND; Pogo_Pad_D2.0mm
ATP34: TP_JUMP_WAKE; Pogo_Pad_S2.0mm
ATP35: TP_MP25_GND1; Pogo_Pad_D2.0mm
ATP36: TP_MP25_GND2; Pogo_Pad_D2.0mm
ATP37: TP_NRST; Pogo_Pad_D2.0mm
ATP38: TP_SPI_CS_FIN; Pogo_Pad_D2.0mm
ATP39: TP_SPI_MISO; Pogo_Pad_D2.0mm
ATP40: TP_SPI_MOSI; Pogo_Pad_S2.0mm
ATP41: TP_SPI_SCLK; Pogo_Pad_D2.0mm
ATP42: TP_SWCLK; Pogo_Pad_D2.0mm
ATP43: TP_SWDIO; Pogo_Pad_D2.0mm
ATP44: TP_SWO; Pogo_Pad_D2.0mm
ATP45: TP_VDD; Pogo_Pad_S2.0mm
AU1: CD74HC4514PW; SOP65P640X120-24N; MPN CD74HC4514PW
AU2: TCAN1042GVDQ1; SOIC127P600X175-8N; MPN TCAN1042GVDQ1

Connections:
3V3: AJ1.1, AJ1.45, AJ1.51, ATP30.1, AU2.5 (VIO)
3V3_AON: AJ1.2, AJ1.46, ATP45.1
ACTIVATE_CONFIRM: AJ1.3, AR2.2, AR3.1, ATP1.1
ACTIVATE_HV: AJ1.28, AJ1.50, AQ17.4 (S), AR1.1, AR2.1, AR4.1
ACTIVATE_SET: AJ1.4, AQ18.1 (G), ATP2.1
ACTIVATION_UNLOCK: AP1.1, AQ17.1 (D_1), AQ17.2 (D_2), AQ17.5 (D_3), AQ17.6 (D_4)
ACTIVATION_UNLOCK_G: AQ17.3 (G), AR4.2, AR5.1
ACTIVATION_UNLOCK_GD: AQ18.3 (D), AR5.2
ACT_WIRE_0: AP2.1, AQ1.3 (D)
ACT_WIRE_1: AP3.1, AQ2.3 (D)
ACT_WIRE_2: AP4.1, AQ3.3 (D)
ACT_WIRE_3: AP5.1, AQ4.3 (D)
ACT_WIRE_4: AP6.1, AQ5.3 (D)
ACT_WIRE_5: AP7.1, AQ6.3 (D)
ACT_WIRE_6: AP8.1, AQ7.3 (D)
ACT_WIRE_7: AP9.1, AQ8.3 (D)
ACT_WIRE_8: AP10.1, AQ9.3 (D)
ACT_WIRE_9: AP11.1, AQ10.3 (D)
ACT_WIRE_10: AP12.1, AQ11.3 (D)
ACT_WIRE_11: AP13.1, AQ12.3 (D)
ACT_WIRE_12: AP14.1, AQ13.3 (D)
ACT_WIRE_13: AP15.1, AQ14.3 (D)
ACT_WIRE_14: AP16.1, AQ15.3 (D)
ACT_WIRE_15: AP17.1, AQ16.3 (D)
BAT_PROT: AJ1.5, AJ1.47, ATP3.1, AU1.1 (~LE), AU1.24 (VCC)
BAT_RAW: AJ1.6, AJ1.48, ATP4.1
BOOT0: AJ1.7, ATP5.1
COMP_5V: AC1.1, AJ1.8, AJ1.49, AU2.3 (VCC)
COMP_SWDCLK: AJ1.9, ATP42.1
COMP_SWDIO: AJ1.10, ATP43.1
EXT_CAN_N: AR6.2, ATP6.1, AU2.6 (CANL)
EXT_CAN_P: AR6.1, ATP7.1, AU2.7 (CANH)
EXT_CAN_RX: AJ1.16, AU2.4 (RXD)
EXT_CAN_TX: AJ1.12, AU2.1 (TXD)
FIN1_AOUT1: AJ1.13, ATP8.1
FIN1_AOUT2: AJ1.14, ATP9.1
FIN1_BOUT1: AJ1.15, ATP10.1
FIN1_BOUT2: AJ1.11, ATP11.1
FIN2_AOUT1: AJ1.17, ATP12.1
FIN2_AOUT2: AJ1.18, ATP13.1
FIN2_BOUT1: AJ1.19, ATP14.1
FIN2_BOUT2: AJ1.20, ATP15.1
FIN3_AOUT1: AJ1.21, ATP16.1
FIN3_AOUT2: AJ1.22, ATP17.1
FIN3_BOUT1: AJ1.23, ATP18.1
FIN3_BOUT2: AJ1.24, ATP19.1
FIN4_AOUT1: AJ1.25, ATP20.1
FIN4_AOUT2: AJ1.30, ATP21.1
FIN4_BOUT1: AJ1.27, ATP22.1
FIN4_BOUT2: AJ1.26, ATP23.1
FIN_HALL: AJ1.29, ATP24.1
FLEX_GND: AC1.2, AJ1.31, AJ1.52, AJ1.53, AJ1.54, AJ1.55, AJ1.56, AJ1.57, AJ1.58, AJ1.59, AJ1.60, AJ1.61, AJ1.62, AJ1.63, AJ1.64, AJ1.65, AJ1.66, AJ1.67, AJ1.68, AJ1.69, AJ1.70, AJ1.71, AJ1.72, AJ1.73, AJ1.74, AJ1.75, AJ1.76, AJ1.77, AJ1.78, AJ1.79, AJ1.80, AJ1.81, AJ1.82, AJ1.83, AJ1.84, AJ1.85, AJ1.86, AJ1.87, AJ1.88, AJ1.89, AJ1.90, AJ1.91, AJ1.92, AJ1.93, AJ1.94, AJ1.95, AJ1.96, AJ1.97, AJ1.98, AQ1.2 (S), AQ2.2 (S), AQ3.2 (S), AQ4.2 (S), AQ5.2 (S), AQ6.2 (S), AQ7.2 (S), AQ8.2 (S), AQ9.2 (S), AQ10.2 (S), AQ11.2 (S), AQ12.2 (S), AQ13.2 (S), AQ14.2 (S), AQ15.2 (S), AQ16.2 (S), AQ18.2 (S), AR1.2, AR3.2, ATP25.1, ATP33.1, ATP35.1, ATP36.1, AU1.12 (GND), AU1.23 (~E), AU2.2 (GND), AU2.8 (STB)
GPIO_EXT_0: AJ1.32, ATP26.1, AU1.2 (A0)
GPIO_EXT_1: AJ1.33, ATP27.1, AU1.3 (A1)
GPIO_EXT_2: AJ1.34, ATP28.1, AU1.21 (A2)
GPIO_EXT_3: AJ1.35, ATP29.1, AU1.22 (A3)
JUMP_PAD: AR7.1, ATP34.1
JUMP_WAKE: AJ1.36, AR7.2
NRST: AJ1.37, ATP37.1
SWO: AJ1.38, ATP44.1
SYS_I2C_SCL: AJ1.39, ATP31.1
SYS_I2C_SDA: AJ1.40, ATP32.1
SYS_SPI_CS_FIN: AJ1.41, ATP38.1
SYS_SPI_MISO: AJ1.42, ATP39.1
SYS_SPI_MOSI: AJ1.43, ATP40.1
SYS_SPI_SCLK: AJ1.44, ATP41.1
Y0_ACTIVATE_SEL: AQ1.1 (G), AU1.11 (Y0)
Y1_ACTIVATE_SEL: AQ2.1 (G), AU1.9 (Y1)
Y2_ACTIVATE_SEL: AQ3.1 (G), AU1.10 (Y2)
Y3_ACTIVATE_SEL: AQ4.1 (G), AU1.8 (Y3)
Y4_ACTIVATE_SEL: AQ5.1 (G), AU1.7 (Y4)
Y5_ACTIVATE_SEL: AQ6.1 (G), AU1.6 (Y5)
Y6_ACTIVATE_SEL: AQ7.1 (G), AU1.5 (Y6)
Y7_ACTIVATE_SEL: AQ8.1 (G), AU1.4 (Y7)
Y8_ACTIVATE_SEL: AQ9.1 (G), AU1.18 (Y8)
Y9_ACTIVATE_SEL: AQ10.1 (G), AU1.17 (Y9)
Y10_ACTIVATE_SEL: AQ11.1 (G), AU1.20 (Y10)
Y11_ACTIVATE_SEL: AQ12.1 (G), AU1.19 (Y11)
Y12_ACTIVATE_SEL: AQ13.1 (G), AU1.14 (Y12)
Y13_ACTIVATE_SEL: AQ14.1 (G), AU1.13 (Y13)
Y14_ACTIVATE_SEL: AQ15.1 (G), AU1.16 (Y14)
Y15_ACTIVATE_SEL: AQ16.1 (G), AU1.15 (Y15)

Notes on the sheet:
A_bottom
Rail decoupling - no pin declared
SPI
FIN 1
FIN 3
FIN 2
FIN 4
CAN
BAT
ACTIVATE
GROUND
ACTIVATION_UNLOCK
HALL
I2C
JUMPSTART
PROGRAM_MP25
GPIO

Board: 14 copper layers, 91 parts (62 on the bottom side), 82 nets, no tracks yet.
